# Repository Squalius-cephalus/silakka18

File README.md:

# Silakka18
RP2040 based macropad with hotswap sockets. Microcontroller uses QMK firmware with Vial support. Based on the [Silli18](https://github.com/Squalius-cephalus/silli18 "Silli18") project, but the firmware is not compatible between them.

## Bill of materials

 - 1 x PCB
 - 1 x Pin compatible Raspberry Pi Pico
 - 1 x 3D printed bottom plate
 - 1 x 3D printed top plate
 - 2 x EC11 Rotary encoders
 - 16 x MX style mechanical switches
 - 16 x MX compatible keycaps
 - 16 x Kailh Hotswap Sockets
 - 8 x M2 4mm bolt
 - 8 x M2 brass inserts 
 - 8x Rubber feet

## TODO

 1. Make build guide

PCB design uses footprints from [ScottoKeebs](https://github.com/joe-scotto/scottokeebs/tree/main/Extras/ScottoKicad "ScottoKeebs") and [kbd library.](https://github.com/foostan/kbd "kbd library.")

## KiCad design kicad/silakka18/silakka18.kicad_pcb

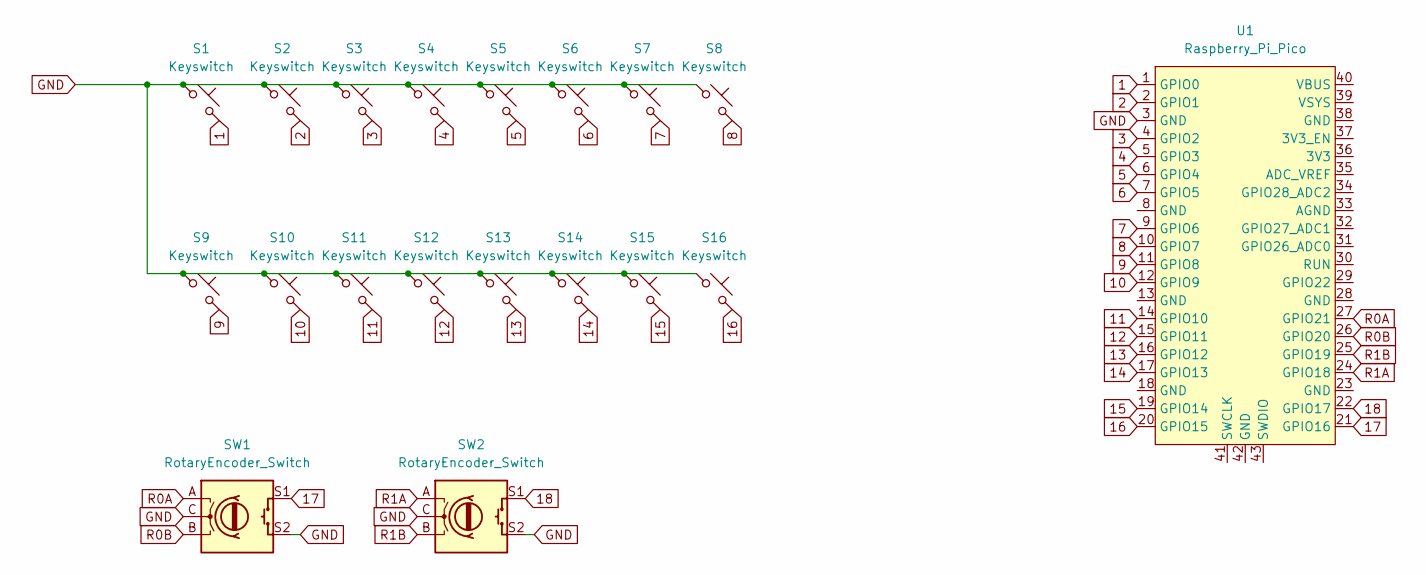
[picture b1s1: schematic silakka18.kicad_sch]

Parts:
S1, S2, S3, S4, S5, S6, S7, S8, S9, S10, S11, S12, S13, S14, S15, S16: Keyswitch; CherryMX_Hotswap
SW1, SW2: RotaryEncoder_Switch; RotaryEncoder_EC11
U1: Raspberry_Pi_Pico

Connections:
1: S1.2, U1.1 (GPIO0)
2: S2.2, U1.2 (GPIO1)
3: S3.2, U1.4 (GPIO2)
4: S4.2, U1.5 (GPIO3)
5: S5.2, U1.6 (GPIO4)
6: S6.2, U1.7 (GPIO5)
7: S7.2, U1.9 (GPIO6)
8: S8.2, U1.10 (GPIO7)
9: S9.2, U1.11 (GPIO8)
10: S10.2, U1.12 (GPIO9)
11: S11.2, U1.14 (GPIO10)
12: S12.2, U1.15 (GPIO11)
13: S13.2, U1.16 (GPIO12)
14: S14.2, U1.17 (GPIO13)
15: S15.2, U1.19 (GPIO14)
16: S16.2, U1.20 (GPIO15)
17: SW1.S1, U1.21 (GPIO16)
18: SW2.S1, U1.22 (GPIO17)
GND: S1.1, S2.1, S3.1, S4.1, S5.1, S6.1, S7.1, S8.1, S9.1, S10.1, S11.1, S12.1, S13.1, S14.1, S15.1, S16.1, SW1.C, SW1.S2, SW2.C, SW2.S2, U1.3 (GND)
R0A: SW1.A, U1.27 (GPIO21)
R0B: SW1.B, U1.26 (GPIO20)
R1A: SW2.A, U1.24 (GPIO18)
R1B: SW2.B, U1.25 (GPIO19)

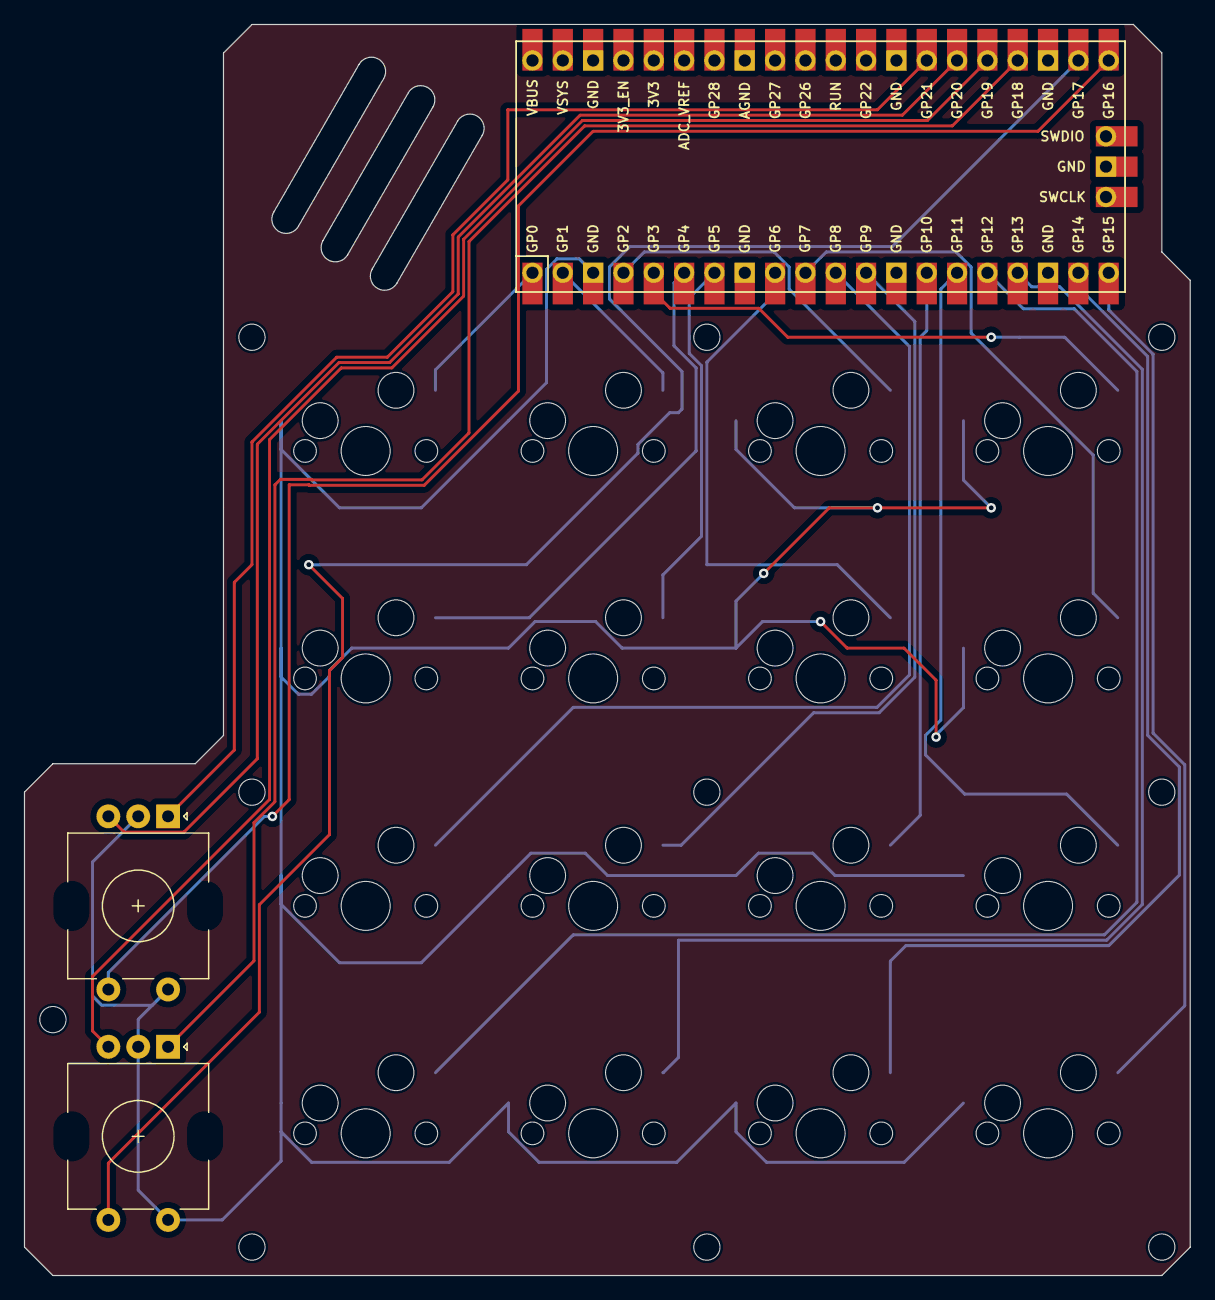
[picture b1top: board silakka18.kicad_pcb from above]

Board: 2 copper layers, 97.6 x 104.8 mm, 19 parts (0 on the bottom side), 23 nets.
